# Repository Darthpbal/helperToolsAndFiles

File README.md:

# helperToolsAndFiles
A place to keep things like various cheat sheets or programs/tools/etc I can use to make development easier.

the product directory contains standalone applications or versions of small apps in different languages

Docker directory contains a docker server source files for simulating a server on my desktop for running a php/mySql server locally

Langauges directory contains folders for all practicing languages. 

cheatsheets directory is just various sets of useful information that is either general or otherwise applicable to all/many languages or not to any language at all.

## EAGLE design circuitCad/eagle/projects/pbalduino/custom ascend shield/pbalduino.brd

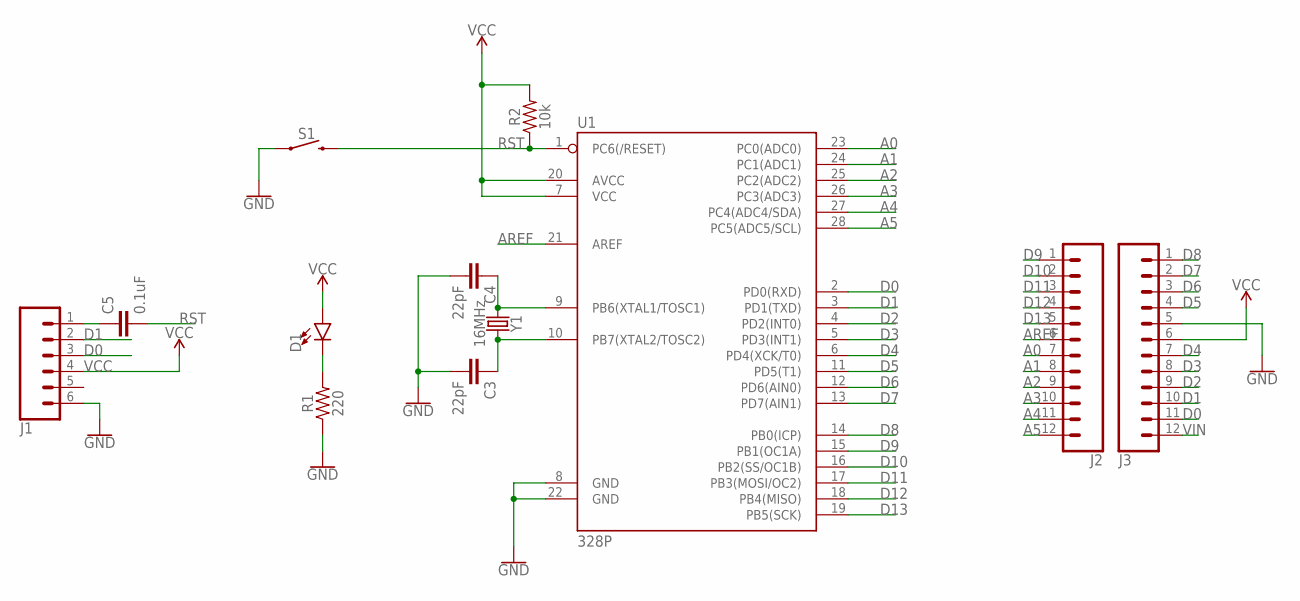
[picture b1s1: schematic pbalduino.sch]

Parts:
C3, C4: 22pF; CAP-PTH-2.54
C5: 0.1uF; CAP-PTH-SMALL-KIT
D1: LED-3MM-NO_SILK; LED_3MM-NS
J1: CONN_06LOCK; 1X06_LOCK
J2, J3: CONN_12; 1X12
R1: 220; AXIAL-0.1
R2: 10k; AXIAL-0.1
S1: MOMENTARY-SWITCH-SPST-PTH-6.0MM; TACTILE_SWITCH_PTH_6.0MM
U1: 328P; DIP28
Y1: 16MHz; HC49US

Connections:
A0: J2.7, U1.23 (PC0(ADC0))
A1: J2.8, U1.24 (PC1(ADC1))
A2: J2.9, U1.25 (PC2(ADC2))
A3: J2.10, U1.26 (PC3(ADC3))
A4: J2.11, U1.27 (PC4(ADC4/SDA))
A5: J2.12, U1.28 (PC5(ADC5/SCL))
AREF: J2.6, U1.21 (AREF)
D0: J1.3, J3.11, U1.2 (PD0(RXD))
D1: J1.2, J3.10, U1.3 (PD1(TXD))
D2: J3.9, U1.4 (PD2(INT0))
D3: J3.8, U1.5 (PD3(INT1))
D4: J3.7, U1.6 (PD4(XCK/T0))
D5: J3.4, U1.11 (PD5(T1))
D6: J3.3, U1.12 (PD6(AIN0))
D7: J3.2, U1.13 (PD7(AIN1))
D8: J3.1, U1.14 (PB0(ICP))
D9: J2.1, U1.15 (PB1(OC1A))
D10: J2.2, U1.16 (PB2(SS/OC1B))
D11: J2.3, U1.17 (PB3(MOSI/OC2))
D12: J2.4, U1.18 (PB4(MISO))
D13: J2.5, U1.19 (PB5(SCK))
GND: C3.2, C4.2, J1.6, J3.5, R1.P$1 (1), S1.1, U1.8 (GND), U1.22 (GND)
unnamed: C5.1, J1.1
unnamed: C3.1, U1.10 (PB7(XTAL2/TOSC2)), Y1.2
unnamed: C4.1, U1.9 (PB6(XTAL1/TOSC1)), Y1.1
unnamed: D1.K (C), R1.P$2 (2)
RST: C5.2, R2.P$1 (1), S1.3 (2), U1.1 (PC6(/RESET))
VCC: D1.A, J1.4, J3.6, R2.P$2 (2), U1.7 (VCC), U1.20 (AVCC)
VIN: J3.12

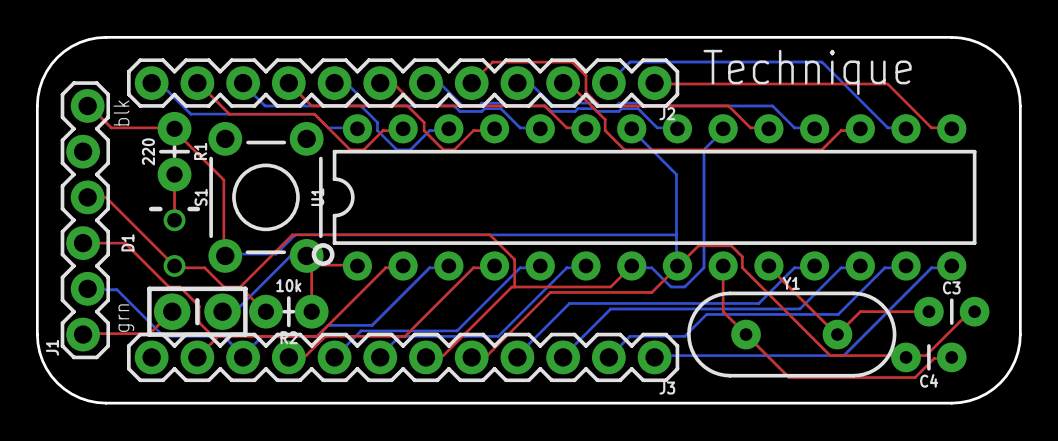
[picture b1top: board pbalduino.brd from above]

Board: 2 copper layers, 54.6 x 20.3 mm, 12 parts (0 on the bottom side), 28 nets.

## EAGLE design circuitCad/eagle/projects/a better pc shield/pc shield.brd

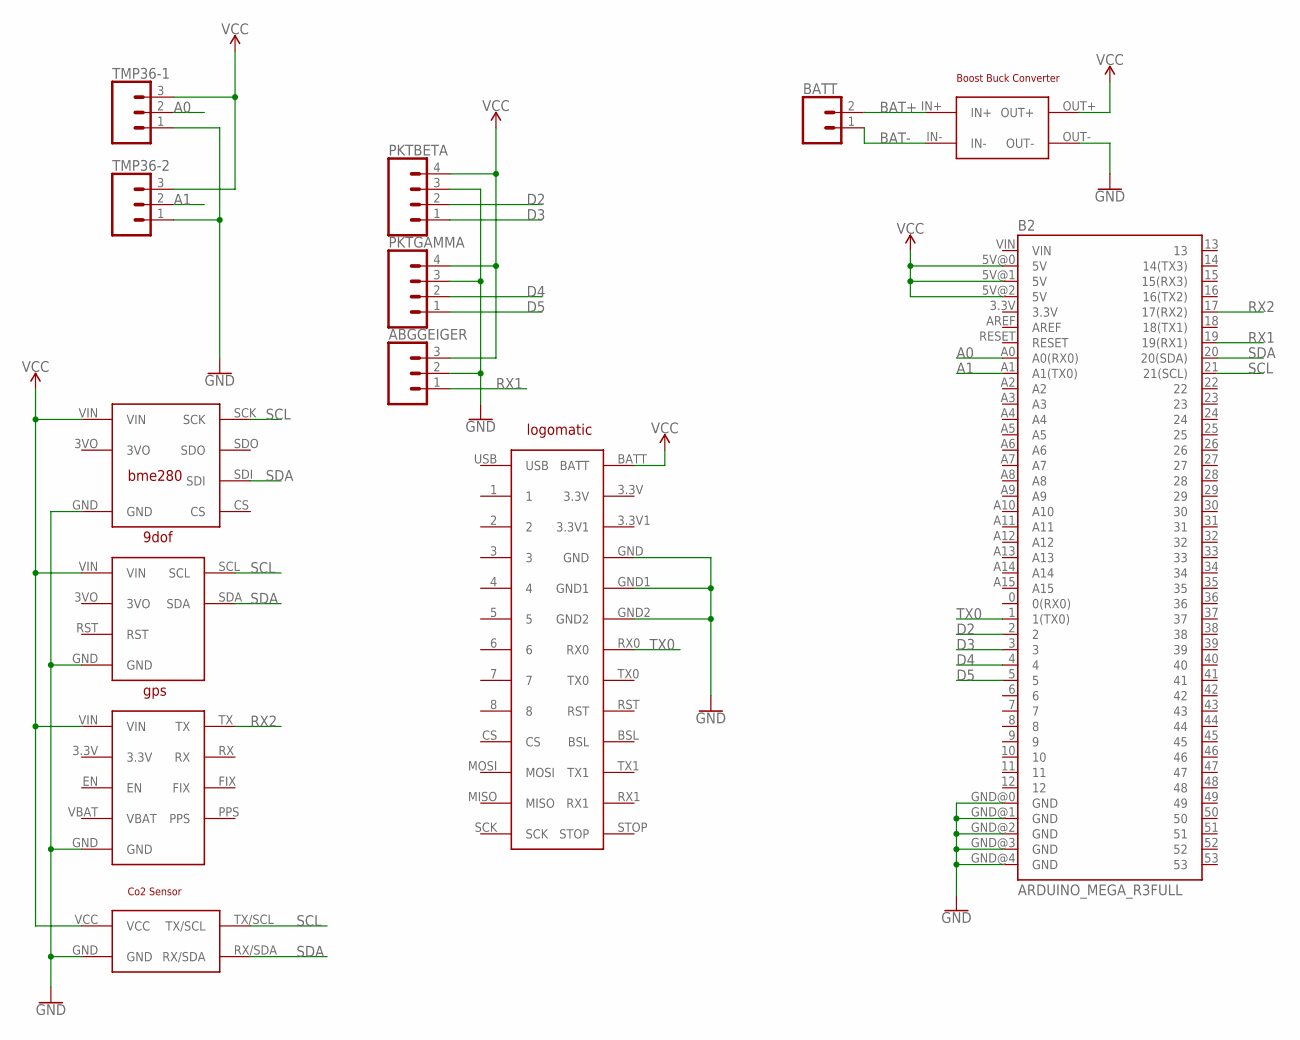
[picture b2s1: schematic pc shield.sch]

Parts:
ABGGEIGER: CONN_03; 1X03
B2: ARDUINO_MEGA_R3FULL; ARDUINO_MEGA
BATT: CONN_02; 1X02
PKTBETA: CONN_04; 1X04
PKTGAMMA: CONN_04; 1X04
TMP36-1, TMP36-2: CONN_03; 1X03
U$1: ULTIMATEGPS; ULTIMATEGPSPKG
U$2: BME280; BME280ADAFRUITPKG
U$3: LOGOMATIC; LOGOMATICPKG
U$4: NXP9DOF; NXP9DOFPKG
U$5: CO2SENSOR; CO2INTERFACEBOARDPKG
U$6: BOOSTBUCK; BOOSTBUCKPKG

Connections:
A0: B2.A0 (A0(RX0)), TMP36-1.2
A1: B2.A1 (A1(TX0)), TMP36-2.2
BAT+: BATT.2, U$6.IN+
BAT-: BATT.1, U$6.IN-
D2: B2.2, PKTBETA.2
D3: B2.3, PKTBETA.1
D4: B2.4, PKTGAMMA.2
D5: B2.5, PKTGAMMA.1
GND: ABGGEIGER.2, B2.GND@0 (GND), B2.GND@1 (GND), B2.GND@2 (GND), B2.GND@3 (GND), B2.GND@4 (GND), PKTBETA.3, PKTGAMMA.3, TMP36-1.1, TMP36-2.1, U$1.GND, U$2.GND, U$3.GND, U$3.GND1, U$3.GND2, U$4.GND, U$5.GND, U$6.OUT-
RX1: ABGGEIGER.1, B2.19 (19(RX1))
RX2: B2.17 (17(RX2)), U$1.TX
SCL: B2.21 (21(SCL)), U$2.SCK, U$4.SCL, U$5.TX/SCL
SDA: B2.20 (20(SDA)), U$2.SDI, U$4.SDA, U$5.RX/SDA
TX0: B2.1 (1(TX0)), U$3.RX0
VCC: ABGGEIGER.3, B2.5V@0 (5V), B2.5V@1 (5V), B2.5V@2 (5V), PKTBETA.4, PKTGAMMA.4, TMP36-1.3, TMP36-2.3, U$1.VIN, U$2.VIN, U$3.BATT, U$4.VIN, U$5.VCC, U$6.OUT+

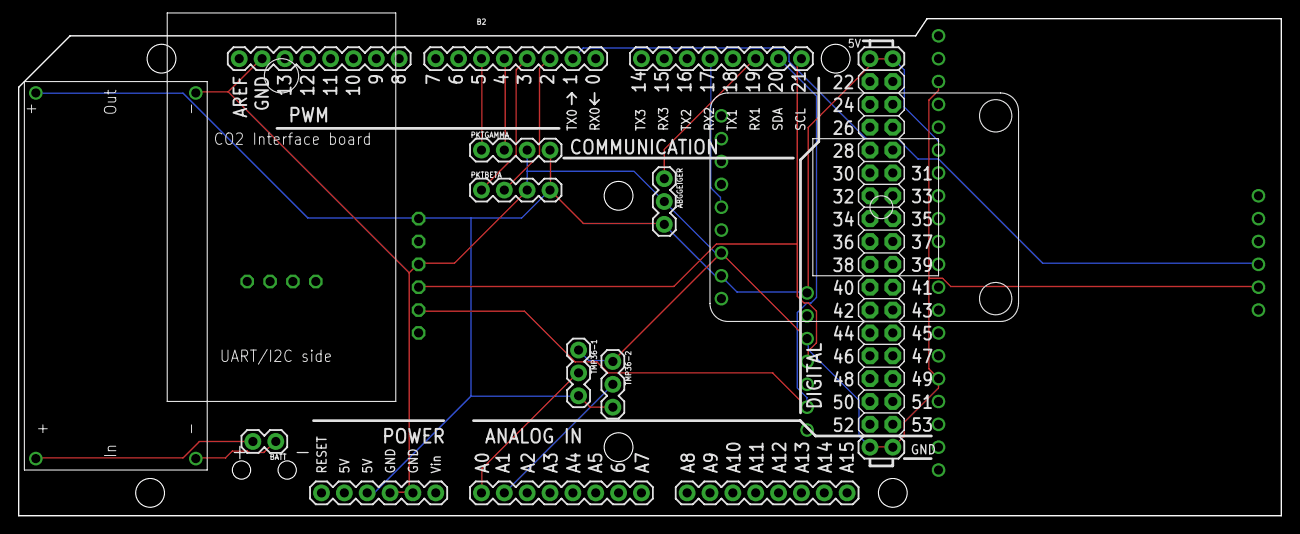
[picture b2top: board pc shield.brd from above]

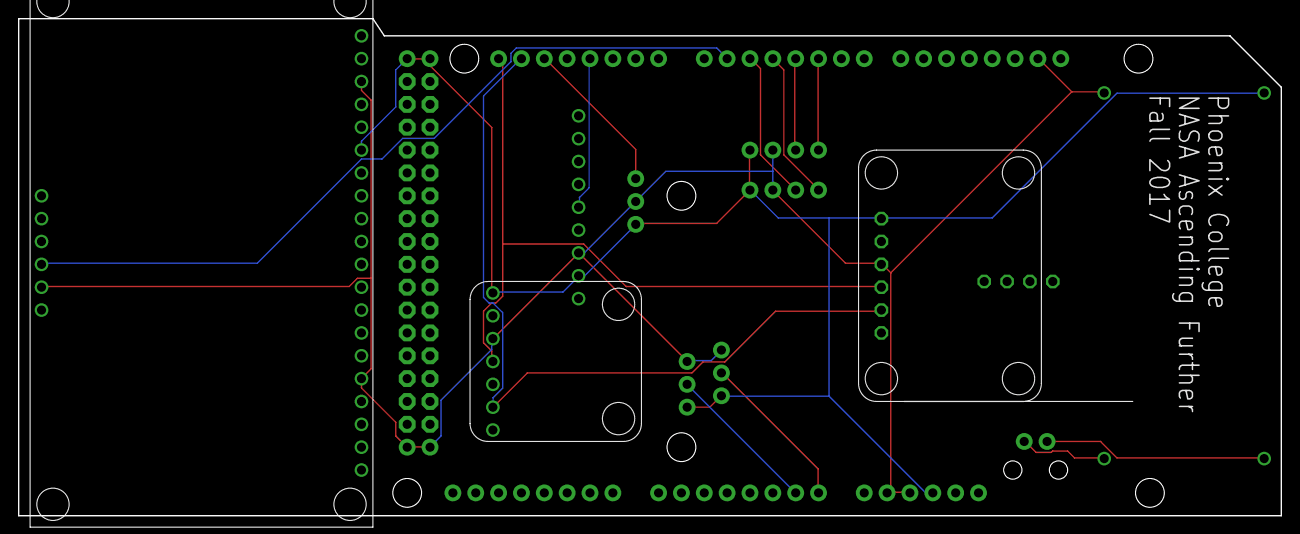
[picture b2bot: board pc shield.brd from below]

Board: 2 copper layers, 140.3 x 55.2 mm, 13 parts (3 on the bottom side), 15 nets.

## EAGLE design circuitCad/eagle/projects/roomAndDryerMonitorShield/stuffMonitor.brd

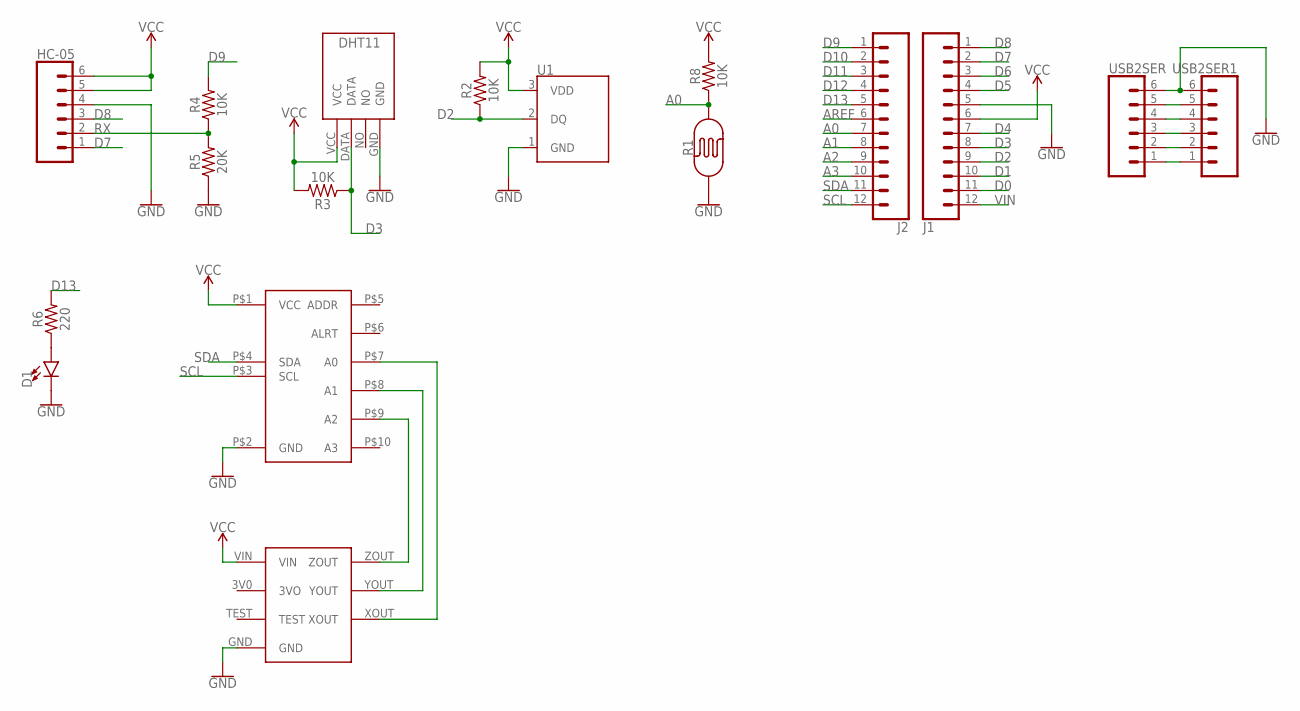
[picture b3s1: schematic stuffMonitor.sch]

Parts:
D1: LED5MM; LED_5MM
HC-05: CONN_06NO_SILK_FEMALE_PTH; 1X06_NO_SILK
J1, J2: CONN_12; 1X12
R1: PHOTOCELLPTH; PHOTOCELL
R2, R3, R4, R8: 10K; AXIAL-0.1
R5: 20K; AXIAL-0.1
R6: 220; AXIAL-0.1
U1: DS18B20; TO-92-AMMO
U$2: SCRAPACCEL; SCRAPACCELANALOG
U$3: 12BITADCADAFRUIT; ADC12BITADAFRUIT
U$4: DHT11-PION.
USB2SER, USB2SER1: CONN_06NO_SILK_FEMALE_PTH; 1X06_NO_SILK

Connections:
A0: J2.7, R1.2, R8.P$1 (1)
A1: J2.8
A2: J2.9
A3: J2.10
AREF: J2.6
D0: J1.11
D1: J1.10
D2: J1.9, R2.P$1 (1), U1.2 (DQ)
D3: J1.8, R3.P$1 (1), U$4.DATA
D4: J1.7
D5: J1.4
D6: J1.3
D7: HC-05.1, J1.2
D8: HC-05.3, J1.1
D9: J2.1, R4.P$2 (2)
D10: J2.2
D11: J2.3
D12: J2.4
D13: J2.5, R6.P$2 (2)
GND: D1.K (C), HC-05.4, J1.5, R1.1, R5.P$1 (1), U1.1 (GND), U$2.GND, U$3.P$2 (GND), U$4.GND, USB2SER.6, USB2SER1.6
unnamed: D1.A, R6.P$1 (1)
unnamed: USB2SER.1, USB2SER1.1
unnamed: USB2SER.2, USB2SER1.2
unnamed: USB2SER.3, USB2SER1.3
unnamed: USB2SER.4, USB2SER1.4
unnamed: USB2SER.5, USB2SER1.5
unnamed: U$2.ZOUT, U$3.P$9 (A2)
unnamed: U$2.YOUT, U$3.P$8 (A1)
unnamed: U$2.XOUT, U$3.P$7 (A0)
RX: HC-05.2, R4.P$1 (1), R5.P$2 (2)
SCL: J2.12, U$3.P$3 (SCL)
SDA: J2.11, U$3.P$4 (SDA)
VCC: HC-05.5, HC-05.6, J1.6, R2.P$2 (2), R3.P$2 (2), R8.P$2 (2), U1.3 (VDD), U$2.VIN, U$3.P$1 (VCC), U$4.VCC
VIN: J1.12

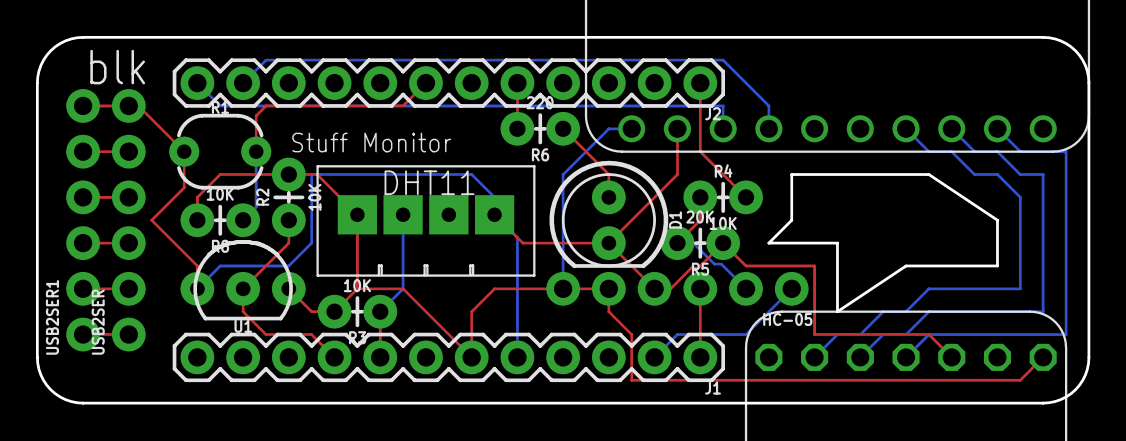
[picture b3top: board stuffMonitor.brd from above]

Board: 2 copper layers, 58.4 x 20.3 mm, 17 parts (0 on the bottom side), 21 nets.

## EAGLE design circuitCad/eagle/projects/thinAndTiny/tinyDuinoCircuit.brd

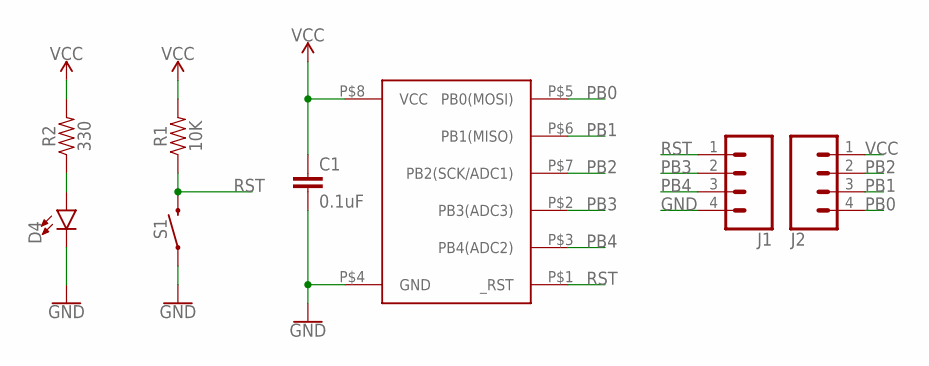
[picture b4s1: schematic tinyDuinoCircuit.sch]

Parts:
C1: 0.1uF; CAP-PTH-SMALL-KIT
D4: LED-3MM-NO_SILK; LED_3MM-NS
J1, J2: CONN_04; 1X04
R1: 10K; AXIAL-0.1
R2: 330; AXIAL-0.1
S1: MOMENTARY-SWITCH-SPST-PTH-6.0MM; TACTILE_SWITCH_PTH_6.0MM
U$1: ATTINY85-DIP8; DIP8

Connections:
GND: C1.2, D4.K (C), J1.4, S1.1, U$1.P$4 (GND)
unnamed: D4.A, R2.P$1 (1)
PB0: J2.4, U$1.P$5 (PB0(MOSI))
PB1: J2.3, U$1.P$6 (PB1(MISO))
PB2: J2.2, U$1.P$7 (PB2(SCK/ADC1))
PB3: J1.2, U$1.P$2 (PB3(ADC3))
PB4: J1.3, U$1.P$3 (PB4(ADC2))
RST: J1.1, R1.P$1 (1), S1.3 (2), U$1.P$1 (_RST)
VCC: C1.1, J2.1, R1.P$2 (2), R2.P$2 (2), U$1.P$8 (VCC)

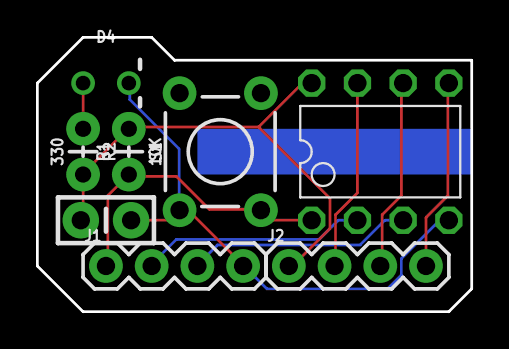
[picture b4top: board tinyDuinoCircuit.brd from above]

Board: 2 copper layers, 24.1 x 15.2 mm, 8 parts (0 on the bottom side), 9 nets.

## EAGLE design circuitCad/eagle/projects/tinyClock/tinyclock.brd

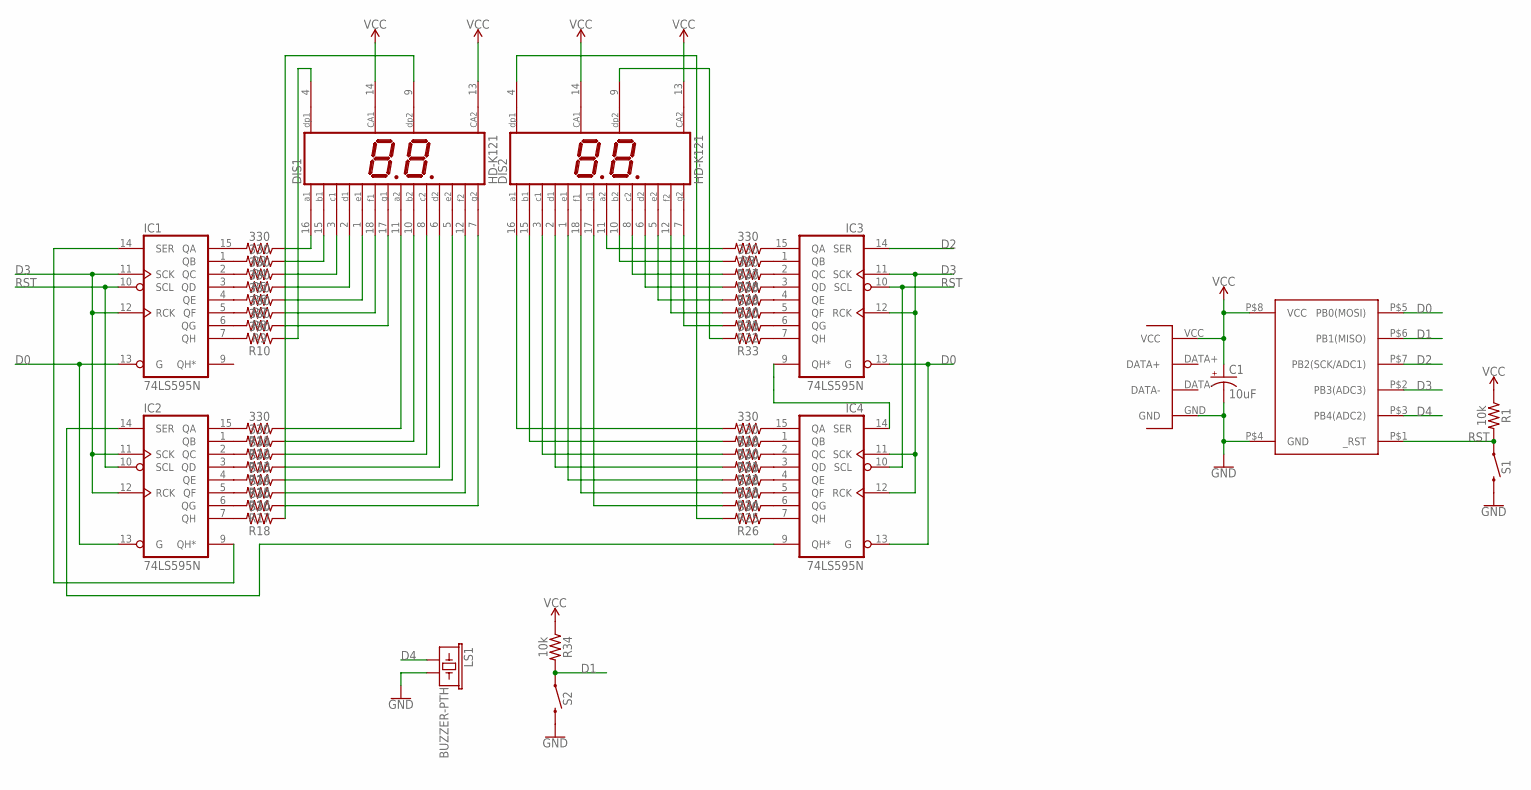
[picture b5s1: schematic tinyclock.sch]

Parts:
C1: 10uF; CPOL-RADIAL-5MM-10MM
DIS1, DIS2: HD-K121; HDSP-R
IC1, IC2, IC3, IC4: 74LS595N; DIL16
LS1: BUZZER-PTH; BUZZER-12MM
R1, R34: 10k; AXIAL-0.1
R2, R3, R4, R5, R6, R7, R8, R9, R10, R11, R12, R13, R14, R15, R16, R17, R18, R19, R20, R21, R22, R23, R24, R25, R26, R27, R28, R29, R30, R31, R32, R33: 330; AXIAL-0.1
S1, S2: MOMENTARY-SWITCH-SPST-PTH-6.0MM; TACTILE_SWITCH_PTH_6.0MM
U$1: ATTINY85-DIP8; DIP8
U$2: USBPCB

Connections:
D0: IC1.13 (G), IC2.13 (G), IC3.13 (G), IC4.13 (G), U$1.P$5 (PB0(MOSI))
D1: R34.P$2 (2), S2.1, U$1.P$6 (PB1(MISO))
D2: IC3.14 (SER), U$1.P$7 (PB2(SCK/ADC1))
D3: IC1.11 (SCK), IC1.12 (RCK), IC2.11 (SCK), IC2.12 (RCK), IC3.11 (SCK), IC3.12 (RCK), IC4.11 (SCK), IC4.12 (RCK), U$1.P$2 (PB3(ADC3))
D4: LS1.+ (1), U$1.P$3 (PB4(ADC2))
GND: C1.-, IC1.8 (GND), IC2.8 (GND), IC3.8 (GND), IC4.8 (GND), LS1.- (2), S1.3 (2), S2.3 (2), U$1.P$4 (GND), U$2.GND
unnamed: IC1.15 (QA), R2.P$2 (2)
unnamed: IC2.14 (SER), IC4.9 (QH*)
unnamed: DIS1.16 (A1), R2.P$1 (1)
unnamed: IC1.1 (QB), R4.P$2 (2)
unnamed: IC1.2 (QC), R5.P$2 (2)
unnamed: IC1.3 (QD), R6.P$2 (2)
unnamed: IC1.4 (QE), R7.P$2 (2)
unnamed: IC1.5 (QF), R8.P$2 (2)
unnamed: IC1.6 (QG), R9.P$2 (2)
unnamed: IC1.7 (QH), R10.P$2 (2)
unnamed: DIS1.15 (B1), R4.P$1 (1)
unnamed: DIS1.3 (C1), R5.P$1 (1)
unnamed: DIS1.2 (D1), R6.P$1 (1)
unnamed: DIS1.1 (E1), R7.P$1 (1)
unnamed: DIS1.18 (F1), R8.P$1 (1)
unnamed: DIS1.17 (G1), R9.P$1 (1)
unnamed: IC2.15 (QA), R11.P$2 (2)
unnamed: IC2.1 (QB), R12.P$2 (2)
unnamed: IC2.2 (QC), R13.P$2 (2)
unnamed: IC2.3 (QD), R14.P$2 (2)
unnamed: IC2.4 (QE), R15.P$2 (2)
unnamed: IC2.5 (QF), R16.P$2 (2)
unnamed: IC2.6 (QG), R17.P$2 (2)
unnamed: IC2.7 (QH), R18.P$2 (2)
unnamed: IC3.15 (QA), R3.P$1 (1)
unnamed: IC3.1 (QB), R27.P$1 (1)
unnamed: IC3.2 (QC), R28.P$1 (1)
unnamed: IC3.3 (QD), R29.P$1 (1)
unnamed: IC3.4 (QE), R30.P$1 (1)
unnamed: IC3.5 (QF), R31.P$1 (1)
unnamed: IC3.6 (QG), R32.P$1 (1)
unnamed: IC3.7 (QH), R33.P$1 (1)
unnamed: IC4.15 (QA), R19.P$1 (1)
unnamed: IC4.1 (QB), R20.P$1 (1)
unnamed: IC4.2 (QC), R21.P$1 (1)
unnamed: IC4.3 (QD), R22.P$1 (1)
unnamed: IC4.4 (QE), R23.P$1 (1)
unnamed: IC4.5 (QF), R24.P$1 (1)
unnamed: IC4.6 (QG), R25.P$1 (1)
unnamed: IC4.7 (QH), R26.P$1 (1)
unnamed: DIS1.4 (DP1), R10.P$1 (1)
unnamed: DIS1.11 (A2), R11.P$1 (1)
unnamed: DIS1.10 (B2), R12.P$1 (1)
unnamed: DIS1.8 (C2), R13.P$1 (1)
unnamed: DIS1.6 (D2), R14.P$1 (1)
unnamed: DIS1.5 (E2), R15.P$1 (1)
unnamed: DIS1.12 (F2), R16.P$1 (1)
unnamed: DIS1.7 (G2), R17.P$1 (1)
unnamed: DIS1.9 (DP2), R18.P$1 (1)
unnamed: DIS2.11 (A2), R3.P$2 (2)
unnamed: DIS2.10 (B2), R27.P$2 (2)
unnamed: DIS2.8 (C2), R28.P$2 (2)
unnamed: DIS2.6 (D2), R29.P$2 (2)
unnamed: DIS2.5 (E2), R30.P$2 (2)
unnamed: DIS2.12 (F2), R31.P$2 (2)
unnamed: DIS2.7 (G2), R32.P$2 (2)
unnamed: DIS2.9 (DP2), R33.P$2 (2)
unnamed: DIS2.16 (A1), R19.P$2 (2)
unnamed: DIS2.15 (B1), R20.P$2 (2)
unnamed: DIS2.3 (C1), R21.P$2 (2)
unnamed: DIS2.2 (D1), R22.P$2 (2)
unnamed: DIS2.1 (E1), R23.P$2 (2)
unnamed: DIS2.18 (F1), R24.P$2 (2)
unnamed: DIS2.17 (G1), R25.P$2 (2)
unnamed: DIS2.4 (DP1), R26.P$2 (2)
unnamed: IC3.9 (QH*), IC4.14 (SER)
unnamed: IC1.14 (SER), IC2.9 (QH*)
RST: IC1.10 (SCL), IC2.10 (SCL), IC3.10 (SCL), IC4.10 (SCL), R1.P$2 (2), S1.1, U$1.P$1 (_RST)
VCC: C1.+, DIS1.13 (CA2), DIS1.14 (CA1), DIS2.13 (CA2), DIS2.14 (CA1), IC1.16 (VCC), IC2.16 (VCC), IC3.16 (VCC), IC4.16 (VCC), R1.P$1 (1), R34.P$1 (1), U$1.P$8 (VCC), U$2.VCC

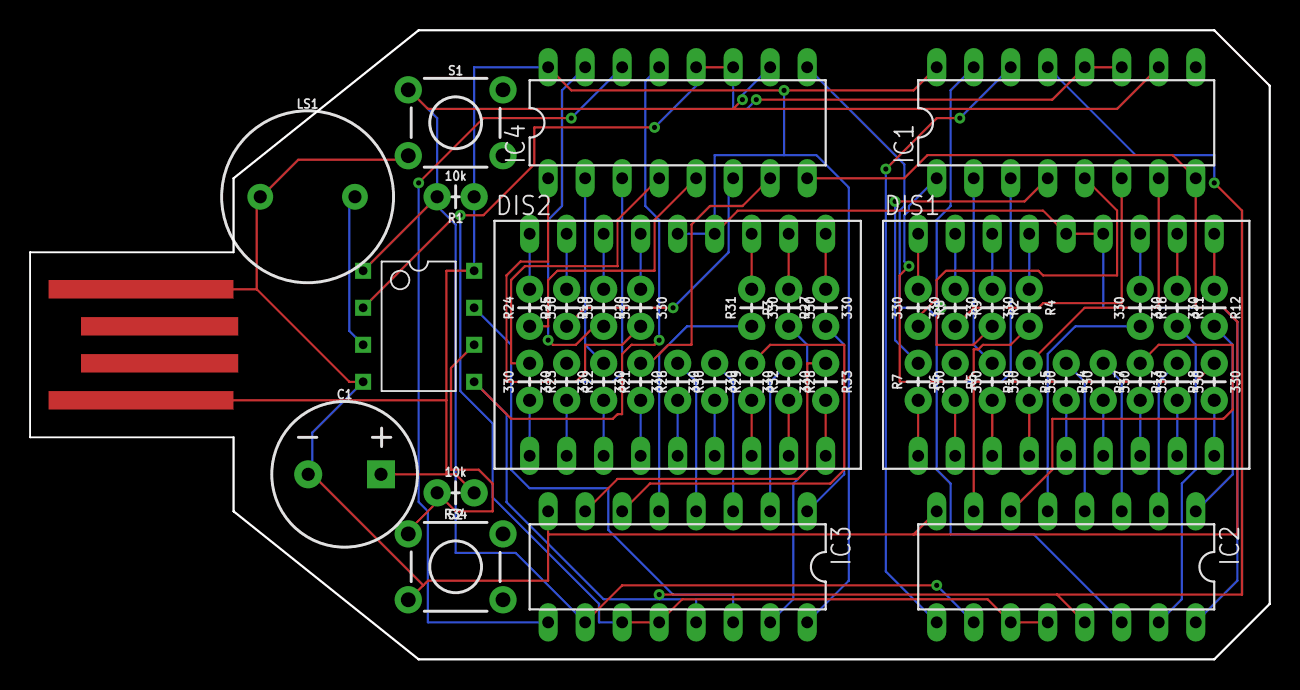
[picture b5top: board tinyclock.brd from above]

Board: 2 copper layers, 85.1 x 43.2 mm, 46 parts (0 on the bottom side), 75 nets.

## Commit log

2015-07-31 added stuff to termianl cheat sheet
2015-11-26 added reading tool c++ program
2015-12-16 getting up to date
2015-12-19 added some stuff after losing my job
2015-12-19 added some more stuff
2015-12-19 added some cheat sheets
2015-12-23 renamed the section analysis program and moved it to a different directory
2016-03-16 added git ignore file
2016-03-16 fixed the git ignore path
2016-03-16 added shopping list tool
2016-04-05 changed the output of the shopping list program to output an html file for better rendering on the dropbox app on mobile
2016-04-24 added cpp class notes to a new language directory
2016-04-24 moved actual products to their own directory
2016-04-24 reorganized directory structure so language resources are in one area, products in another and general cheatsheets in another
2016-04-24 modified the readme to have a little more detail.
2016-04-24 added cpp version of shopping list product source files
2016-04-24 modified makefile for a displayoptions program and added source file for same program
2016-04-24 added display options program source file
2016-04-24 established basic functions for shopping list generator but based in CPP
2016-04-24 added functionality for adding new items to the shopping list and index file.
2016-04-24 changed the level of precision for printing 2 places past the decimal point on numbers.
2016-04-24 mod gitignore
2016-04-24 added a readme
2016-04-24 mod git ignore hope it works
2016-04-24 lasssss
2016-04-24 added proof of concept for abstracting multi textfile creation out to a function for cleaner looking code.
2016-04-24 modified file creation to use a function
2016-04-24 reorganized public members to be more like cronological order
2016-04-24 modified git ignore
2016-04-25 added a todo list
2016-04-26 modified the makefile and removed the dedicated C file for displaying shopping list options.
2016-04-26 Abstracted out all custom functions to a helper source and header file that houses all of the funcitons. Purely and aesthetic change.
2016-04-26 removed some spacing between member functions
2016-04-26 changed the body of the main function to allow running the display options function as well as the shopping list generation function. Also all of the helper functions defined under main was removed s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
2016-05-10 Added a couple of todos based on some things about the program behavior I'd like to improve
2016-07-11 Added some files, moved some files, and added a proof of concept for using the sfml graphics library in cpp
2016-07-29 added conceptual ideas
2016-09-11 added switch case calculator example
2016-09-11 added switchcase calc
2016-11-15 reorganized and renamed some stuff and added python to my languages
2016-11-25 progressed through the lesson
2016-12-15 added a 60 second timer project based in fpga
2016-12-15 python intro
2016-12-15 added more shit
2016-12-21 added an hour counter displayed on the led array
2016-12-21 tweak
2016-12-21 dunno
2017-01-08 added sim5218 gps program
2017-01-08 removed vivado folder
2017-01-08 small edits
2017-01-21 formatting
2017-01-21 new programs
2017-01-26 added accelerometer sources
2017-01-26 added gyro files
2017-03-03 lotsa shit
2017-03-03 added configuration file
2017-03-06 added new IMU files
2017-03-09 added files for arduino ultimate gps
2017-03-09 renamed and reorganized some files
2017-03-09 added the raw output of the GPS to a text file for reference.
2017-03-09 moved the references from the bottom of the main program and put into the reference file.
2017-03-09 corrected serial printing for a single character sample inserted into a c string
2017-03-09 get ahold of myself
2017-03-09 implemented my SIM5218 gps functions but used to watch for the ultimategps tags, however I'm getting some error output
2017-03-09 implemented the SIM5218 based serial functions for operating the ultimate GPS board along with added some result files from a run collecting plenty of data for analyzing some error lines I've noticed.
2017-03-09 added an example found online for delimiting strings from the serial read...fucking annoying.
2017-03-09 added a delay that fixes all of the error lines.
2017-03-09 extended the delay and got rid of the extra newline character print.
2017-03-09 made my example files match up and added a note on program size
2017-03-13 added co2 library files
2017-03-13 trying to fix files not showing up on remote branch
2017-03-13 fix this madness ugh
2017-11-03 catchup
2018-01-23 catchup. Gamepad working. Also other stuff
2018-02-04 modded the git ignore file
2018-02-09 updated the ignore to include html reports
2018-02-09 updated the reporting function
2018-10-01 Made User Interface better

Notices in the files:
parts and their libraries:
SparkFun-Boards: Licensing: Creative Commons ShareAlike 4.0 International - https://creativecommons.org/licenses/by-sa/4.0
